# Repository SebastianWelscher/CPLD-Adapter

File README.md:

# CPLD-Adapter

CPLD-Adapter board for using a Xilinx XC9536XL

Get it at Aisler: https://aisler.net/p/JLAMCPYS

# Example

For this example we use the CPLD-Adapter board, the LED-Shield and the Switch-Shield.
For programming, we use the ISE 14.7 WebPack Software and an USB-JTAG Programmer.
You can buy it at https://eckstein-shop.de/Platform-Cable-USB or other distributors like Amazon etc.

# First step: getting and installing the software

There is a lower version of the software. You can find it on the DVD of the Platform-Cable set.

For the last ISE 14.7 WebPack and for licensing create a Account at Xilinx and dowload the last standart version, not the Win10 Version.
You have to customize some files later for working on Win10, because it´s not a supported Version for Win10. 
We do this later.

After installing you have to get a licence for the WebPack Edition.

# Second step: get it run

If you are using Win10, you have to customize some files to run the software likely stable.
Use this following steps: https://www.xilinx.com/support/answers/62380.html

# third step: Your first Project

| Part  | Port |
|------ |------|
| SW 1  | P30  |
| SW 2  | P31  |
| LED 1 | P2   |
| LED 2 | P3   |

The IO-Ports of the Xilinx 9536XL are 5V tolerable so you can use 5V signals for input (from Arduino, etc). 
The output voltage depends on the supply voltage and is about 3,3V.

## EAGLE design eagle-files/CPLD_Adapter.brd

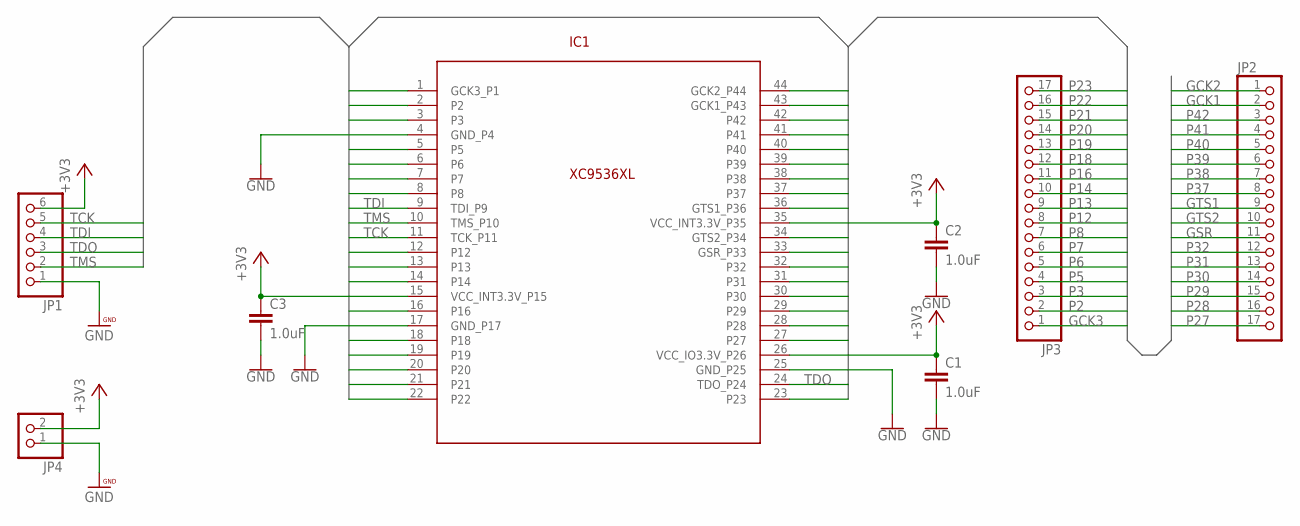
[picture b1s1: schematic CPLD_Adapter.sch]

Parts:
C1, C2, C3: 1.0uF; 0603
IC1: XC9536XL; QFP80P1200X1200X105-44
JP1: PINHD-1X6; 1X06
JP2, JP3: PINHD-1X17; 1X17
JP4: PINHD-1X2; 1X02

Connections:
+3V3: C1.1, C2.1, C3.1, IC1.15 (VCC_INT3.3V_P15), IC1.26 (VCC_IO3.3V_P26), IC1.35 (VCC_INT3.3V_P35), JP1.6, JP4.2
GCK1: IC1.43 (GCK1_P43), JP2.2
GCK2: IC1.44 (GCK2_P44), JP2.1
GCK3: IC1.1 (GCK3_P1), JP3.1
GND: C1.2, C2.2, C3.2, IC1.4 (GND_P4), IC1.17 (GND_P17), IC1.25 (GND_P25), JP1.1, JP4.1
GSR: IC1.33 (GSR_P33), JP2.11
GTS1: IC1.36 (GTS1_P36), JP2.9
GTS2: IC1.34 (GTS2_P34), JP2.10
P2: IC1.2, JP3.2
P3: IC1.3, JP3.3
P5: IC1.5, JP3.4
P6: IC1.6, JP3.5
P7: IC1.7, JP3.6
P8: IC1.8, JP3.7
P12: IC1.12, JP3.8
P13: IC1.13, JP3.9
P14: IC1.14, JP3.10
P16: IC1.16, JP3.11
P18: IC1.18, JP3.12
P19: IC1.19, JP3.13
P20: IC1.20, JP3.14
P21: IC1.21, JP3.15
P22: IC1.22, JP3.16
P23: IC1.23, JP3.17
P27: IC1.27, JP2.17
P28: IC1.28, JP2.16
P29: IC1.29, JP2.15
P30: IC1.30, JP2.14
P31: IC1.31, JP2.13
P32: IC1.32, JP2.12
P37: IC1.37, JP2.8
P38: IC1.38, JP2.7
P39: IC1.39, JP2.6
P40: IC1.40, JP2.5
P41: IC1.41, JP2.4
P42: IC1.42, JP2.3
TCK: IC1.11 (TCK_P11), JP1.5
TDI: IC1.9 (TDI_P9), JP1.4
TDO: IC1.24 (TDO_P24), JP1.3
TMS: IC1.10 (TMS_P10), JP1.2

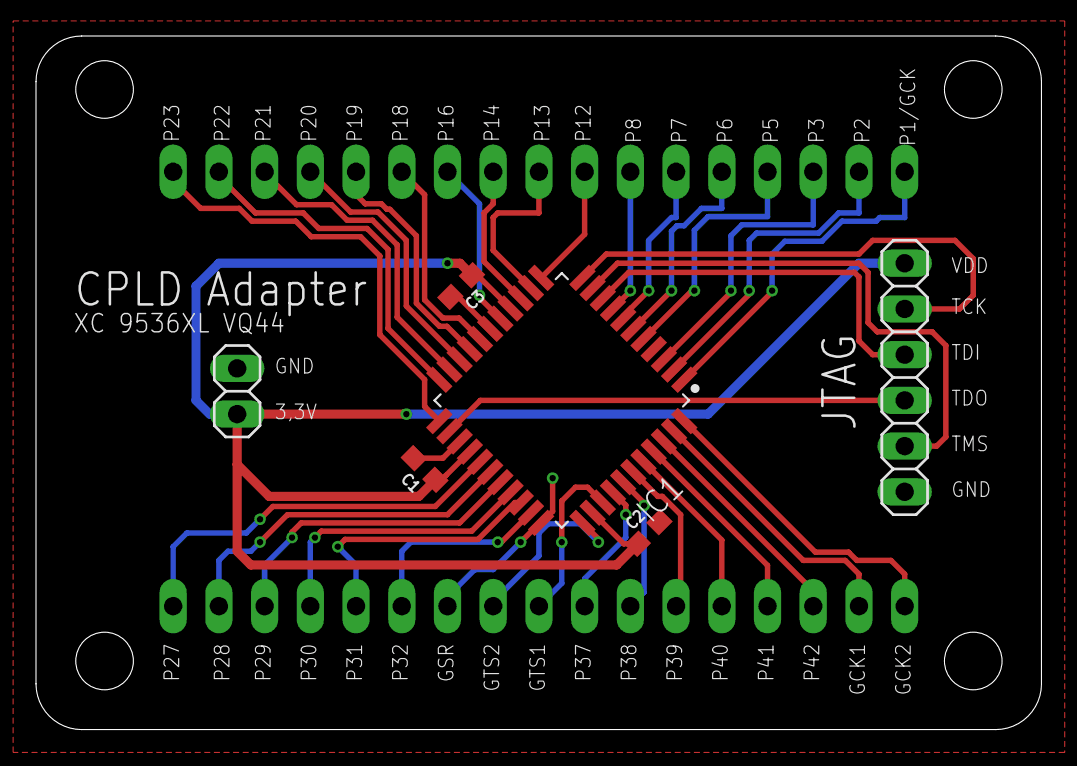
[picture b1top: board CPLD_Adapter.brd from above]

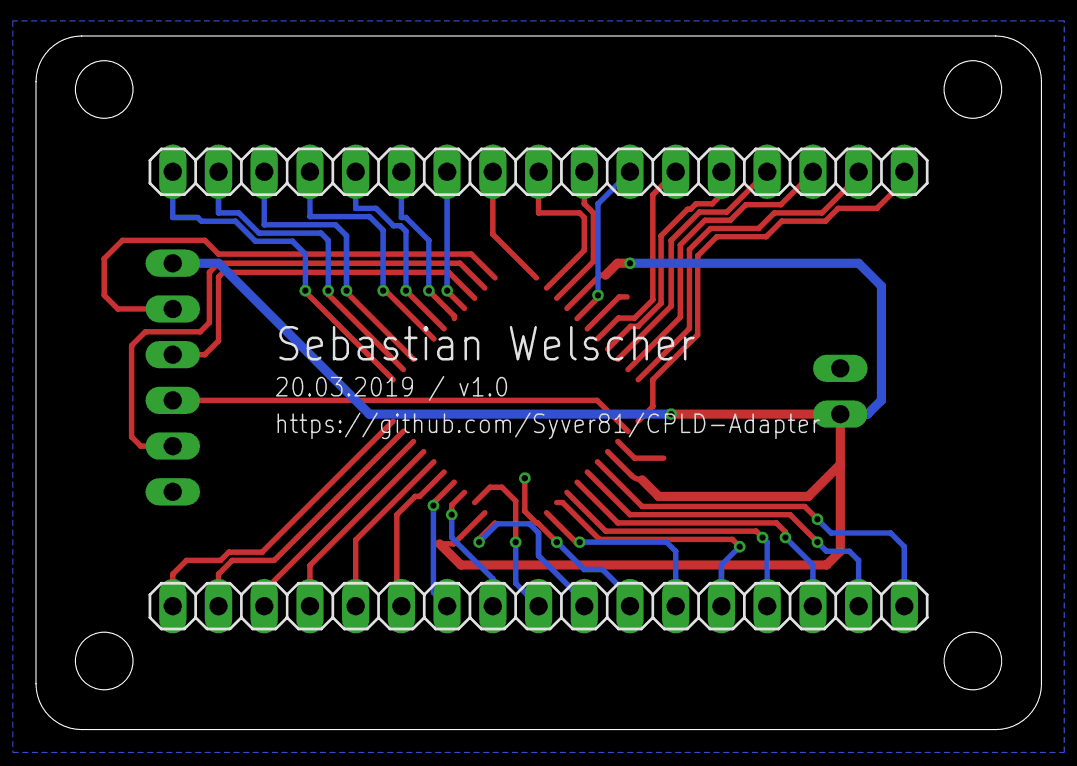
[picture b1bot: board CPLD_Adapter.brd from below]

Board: 2 copper layers, 55.9 x 38.5 mm, 8 parts (2 on the bottom side), 40 nets.

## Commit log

2019-03-23 Create images
2019-03-30 Set theme jekyll-theme-architect

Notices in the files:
parts and their libraries:
SparkFun-Capacitors: Licensing: Creative Commons ShareAlike 4.0 International - https://creativecommons.org/licenses/by-sa/4.0
PatternAgents-Beautify: License : http://creativecommons.org/licenses/by-sa/3.0
(Creative Commons 3.0)
